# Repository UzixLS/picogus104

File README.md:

## PicoGUS/104
Gravis Ultrasound compatible sound card for IBM PC.

This is variant of [PicoGUS](https://picog.us/) v2.0 project by [Ian Scott](https://ianscott.org/) adapted for PC/104 bus. This variant also integrates SAM2695 MIDI synthesizer on board.

For details and firmware please follow this link: https://github.com/polpo/picogus

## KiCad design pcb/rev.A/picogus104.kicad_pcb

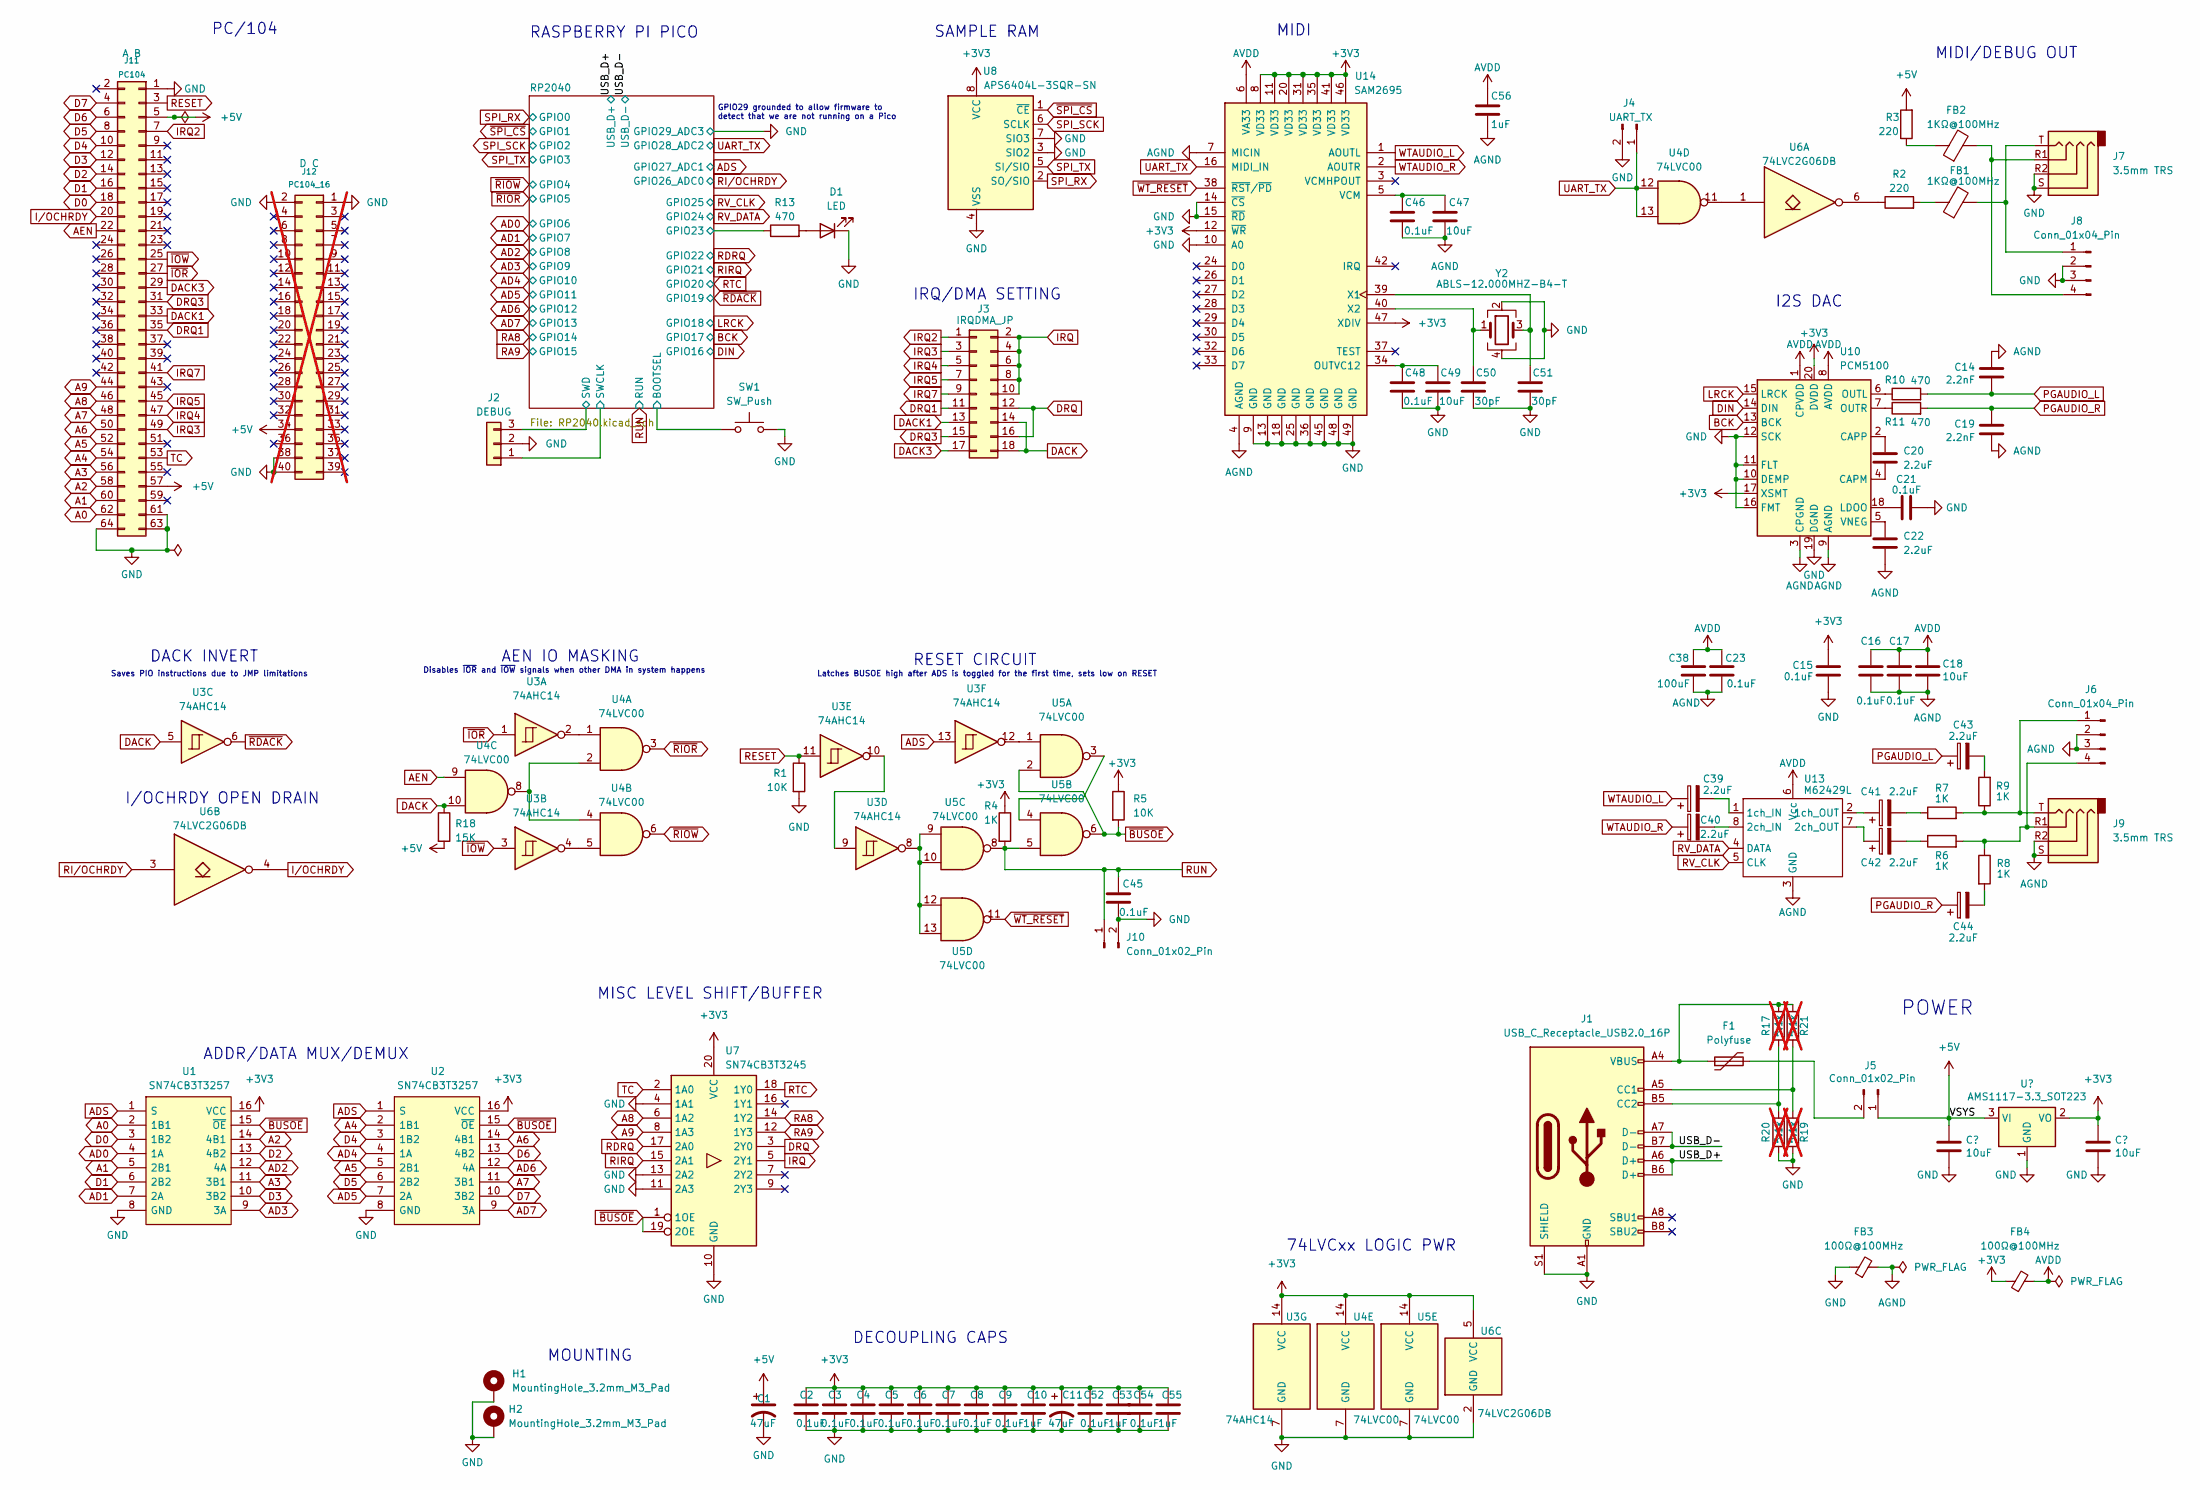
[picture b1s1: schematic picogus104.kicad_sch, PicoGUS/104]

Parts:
C1, C11: 47uF; C_1206_3216Metric
C2, C3, C4, C5, C6, C7, C8, C9, C15, C16, C17, C21, C23, C45, C46, C48, C52, C54: 0.1uF; C_0603_1608Metric_Pad1.08x0.95mm_HandSolder
C10, C53, C55, C56: 1uF; C_0603_1608Metric_Pad1.08x0.95mm_HandSolder
C12, C13, C18, C47, C49: 10uF; C_0805_2012Metric_Pad1.18x1.45mm_HandSolder
C14, C19: 2.2nF; C_0603_1608Metric_Pad1.08x0.95mm_HandSolder
C20, C22: 2.2uF; C_0603_1608Metric_Pad1.08x0.95mm_HandSolder
C38: 100uF; C_1206_3216Metric
C39, C40, C41, C42, C43, C44: 2.2uF; CP_Elec_4x5.4
C50, C51: 30pF; C_0603_1608Metric_Pad1.08x0.95mm_HandSolder
D1: LED; LED_0805_2012Metric_Pad1.15x1.40mm_HandSolder
F1: Polyfuse; Fuse_1812_4532Metric_Pad1.30x3.40mm_HandSolder
FB1, FB2: 1KΩ@100MHz; L_0805_2012Metric_Pad1.05x1.20mm_HandSolder
FB3, FB4: 100Ω@100MHz; L_0805_2012Metric_Pad1.05x1.20mm_HandSolder
H1, H2: MountingHole_3.2mm_M3_Pad
J1: USB_C_Receptacle_USB2.0_16P; USB_C_Receptacle_HRO_TYPE-C-31-M-12
J2: DEBUG; PinHeader_1x03_P2.54mm_Vertical
J3: IRQDMA_JP; PinHeader_2x09_P2.54mm_Vertical
J4: UART_TX; PinHeader_1x02_P2.54mm_Vertical
J5, J10: Conn_01x02_Pin; PinHeader_1x02_P2.54mm_Vertical
J6, J8: Conn_01x04_Pin; PinHeader_1x04_P2.54mm_Vertical
J7, J9: 3.5mm TRS; PJ-322
J11: PC104; PinHeader_2x32_P2.54mm_Vertical
J12: PC104_16; PinHeader_2x20_P2.54mm_Vertical; not fitted
R1, R5: 10K; R_0603_1608Metric_Pad0.98x0.95mm_HandSolder
R2, R3: 220; R_0603_1608Metric_Pad0.98x0.95mm_HandSolder
R4, R6, R7, R8, R9: 1K; R_0603_1608Metric_Pad0.98x0.95mm_HandSolder
R10, R11, R13: 470; R_0603_1608Metric_Pad0.98x0.95mm_HandSolder
R17, R19, R20, R21: 5.1k; R_0603_1608Metric_Pad0.98x0.95mm_HandSolder; not fitted
R18: 15K; R_0603_1608Metric_Pad0.98x0.95mm_HandSolder
SW1: SW_Push; SW_PUSH_6mm
U1, U2: SN74CB3T3257; TSSOP-16_4.4x5mm_P0.65mm; Manufacturer_Part_Number 74FST3257DR2G; Mouser Part Number 863-74FST3257DR2G
U3: 74AHC14; TSSOP-14_4.4x5mm_P0.65mm
U4, U5: 74LVC00; TSSOP-14_4.4x5mm_P0.65mm
U6: 74LVC2G06DB; SOT-23-6_Handsoldering
U7: SN74CB3T3245; TSSOP-20_4.4x6.5mm_P0.65mm
U8: APS6404L-3SQR-SN; SOIC-8_3.9x4.9mm_P1.27mm
U9: AMS1117-3.3_SOT223; SOT-223-3_TabPin2
U10: PCM5100; TSSOP-20_4.4x6.5mm_P0.65mm
U13: M62429L; SOIC-8_3.9x4.9mm_P1.27mm
U14: SAM2695; QFN-48-1EP_6x6mm_P0.4mm_EP4.2x4.2mm
Y2: ABLS-12.000MHZ-B4-T; Crystal_SMD_3225-4Pin_3.2x2.5mm_HandSoldering

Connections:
+3V3: C2.1, C3.1, C4.1, C5.1, C6.1, C7.1, C8.1, C9.1, C10.1, C11.1, C13.1, C15.2, C52.1, C53.1, C54.1, C55.1, FB4.1, R4.1, R5.1, U1.16 (VCC), U2.16 (VCC), U3.14 (VCC), U4.14 (VCC), U5.14 (VCC), U6.5 (VCC), U7.20 (VCC), U8.8 (VCC), U9.2 (VO), U10.17 (XSMT), U10.20 (DVDD), U14.8 (VD33), U14.11 (VD33), U14.12 (~WR), U14.20 (VD33), U14.31 (VD33), U14.35 (VD33), U14.41 (VD33), U14.46 (VD33), U14.47 (XDIV); also elsewhere on the board
+5V: C1.1, C12.1, J5.1, J11.5, J11.57, J12.34, R3.2, R18.2, U9.3 (VI)
/RP2040/GPIO23: R13.1; also elsewhere on the board
/RP2040/SWCLK: J2.1; also elsewhere on the board
/RP2040/SWD: J2.3; also elsewhere on the board
/RP2040/~USB_BOOT: SW1.2; also elsewhere on the board
/USB_D+: J1.A6 (D+), J1.B6 (D+); also elsewhere on the board
/USB_D-: J1.A7 (D-), J1.B7 (D-); also elsewhere on the board
A0: J11.62, U1.2 (1B1)
A1: J11.60, U1.5 (2B1)
A2: J11.58, U1.14 (4B1)
A3: J11.56, U1.11 (3B1)
A4: J11.54, U2.2 (1B1)
A5: J11.52, U2.5 (2B1)
A6: J11.50, U2.14 (4B1)
A7: J11.48, U2.11 (3B1)
A8: J11.46, U7.6 (1A2)
A9: J11.44, U7.8 (1A3)
AD0: U1.4 (1A); also elsewhere on the board
AD1: U1.7 (2A); also elsewhere on the board
AD2: U1.12 (4A); also elsewhere on the board
AD3: U1.9 (3A); also elsewhere on the board
AD4: U2.4 (1A); also elsewhere on the board
AD5: U2.7 (2A); also elsewhere on the board
AD6: U2.12 (4A); also elsewhere on the board
AD7: U2.9 (3A); also elsewhere on the board
ADS: U1.1 (S), U2.1 (S), U3.13; also elsewhere on the board
AEN: J11.22, U4.9
AGND: C14.1, C16.1, C17.1, C18.2, C19.1, C22.2, C23.2, C38.2, C46.1, C47.1, C56.2, FB3.2, J6.2, J6.3, J9.R2, J9.S, U10.3 (CPGND), U10.9 (AGND), U13.3 (GND), U14.4 (AGND), U14.7 (MICIN)
AVDD: C16.2, C17.2, C18.1, C23.1, C38.1, C56.1, FB4.2, U10.1 (CPVDD), U10.8 (AVDD), U13.6 (Vcc), U14.6 (VA33)
BCK: U10.13 (BCK); also elsewhere on the board
D0: J11.18, U1.3 (1B2)
D1: J11.16, U1.6 (2B2)
D2: J11.14, U1.13 (4B2)
D3: J11.12, U1.10 (3B2)
D4: J11.10, U2.3 (1B2)
D5: J11.8, U2.6 (2B2)
D6: J11.6, U2.13 (4B2)
D7: J11.4, U2.10 (3B2)
DACK: J3.14, J3.18, R18.1, U3.5, U4.10
DACK1: J3.13, J11.33
DACK3: J3.17, J11.29
DIN: U10.14 (DIN); also elsewhere on the board
DRQ: J3.12, J3.16, U7.3 (2Y0)
DRQ1: J3.11, J11.35
DRQ3: J3.15, J11.31
GND: C1.2, C2.2, C3.2, C4.2, C5.2, C6.2, C7.2, C8.2, C9.2, C10.2, C11.2, C12.2, C13.2, C15.1, C21.2, C45.2, C48.1, C49.1, C50.1, C51.1, C52.2, C53.2, C54.2, C55.2, D1.1 (K), FB3.1, H1.1, H2.1, J1.A1 (GND), J1.A12 (GND), J1.B1 (GND), J1.B12 (GND), J1.S1 (SHIELD), J2.2, J4.2, J7.R2, J7.S, J8.2, J8.3, J10.2, J11.1, J11.61, J11.63, J11.64, J12.1, J12.2, J12.38, J12.40, R1.2, R19.1, R20.1, SW1.1, U1.8 (GND), U2.8 (GND), U3.7 (GND), U4.7 (GND), U5.7 (GND), U6.2 (GND), U7.4 (1A1), U7.10 (GND), U7.11 (2A3), U7.13 (2A2), U8.3 (SIO2), U8.4 (VSS), U8.7 (SIO3), U9.1 (GND), U10.10 (DEMP), U10.11 (FLT), U10.12 (SCK), U10.16 (FMT), U10.19 (DGND), U14.9 (GND), U14.10 (A0), U14.13 (GND), U14.14 (~CS), U14.15 (~RD), U14.18 (GND), U14.25 (GND), U14.36 (GND), U14.45 (GND), U14.48 (GND), U14.49 (GND), Y2.2, Y2.4; also elsewhere on the board
IRQ: J3.2, J3.4, J3.6, J3.8, J3.10, U7.5 (2Y1)
IRQ2: J3.1, J11.7
IRQ3: J3.3, J11.49
IRQ4: J3.5, J11.47
IRQ5: J3.7, J11.45
IRQ7: J3.9, J11.41
I/OCHRDY: J11.20, U6.4
LRCK: U10.15 (LRCK); also elsewhere on the board
unnamed: C41.2, R7.1
unnamed: C42.2, R6.1
unnamed: C43.2, R9.2
unnamed: C44.2, R8.2
unnamed: D1.2 (A), R13.2
unnamed: F1.1, J1.A4 (VBUS), J1.A9 (VBUS), J1.B4 (VBUS), J1.B9 (VBUS), R17.2, R21.2
unnamed: FB1.1, R2.2
unnamed: FB2.1, R3.1
unnamed: J1.A5 (CC1), R19.2, R21.1
unnamed: J1.B5 (CC2), R17.1, R20.2
unnamed: F1.2, J5.2
unnamed: J6.1, J9.T, R7.2, R9.1
unnamed: J6.4, J9.R1, R6.2, R8.1
unnamed: FB1.2, J7.T, J8.1
unnamed: FB2.2, J7.R1, J8.4
unnamed: R2.1, U6.6
unnamed: U3.2, U4.1
unnamed: U3.4, U4.5
unnamed: U3.8, U5.9, U5.10, U5.12, U5.13
unnamed: U3.9, U3.10
unnamed: U3.12, U5.1
unnamed: U4.2, U4.4, U4.8
unnamed: U4.11, U6.1
unnamed: U5.3, U5.4
unnamed: C20.2, U10.4 (CAPM)
unnamed: C20.1, U10.2 (CAPP)
unnamed: C21.1, U10.18 (LDOO)
unnamed: R10.1, U10.6 (OUTL)
unnamed: R11.1, U10.7 (OUTR)
unnamed: C22.1, U10.5 (VNEG)
unnamed: C39.2, U13.1 (1ch_IN)
unnamed: C41.1, U13.2 (1ch_OUT)
unnamed: C40.2, U13.8 (2ch_IN)
unnamed: C42.1, U13.7 (2ch_OUT)
unnamed: C48.2, C49.2, U14.34 (OUTVC12)
unnamed: C46.2, C47.2, U14.5 (VCM)
unnamed: C51.2, U14.39 (X1), Y2.3
unnamed: C50.2, U14.40 (X2), Y2.1
PGAUDIO_L: C14.2, C43.1, R10.2
PGAUDIO_R: C19.2, C44.1, R11.2
RA8: U7.14 (1Y2); also elsewhere on the board
RA9: U7.12 (1Y3); also elsewhere on the board
RDRQ: U7.17 (2A0); also elsewhere on the board
RESET: J11.3, R1.1, U3.11
RIRQ: U7.15 (2A1); also elsewhere on the board
RI/OCHRDY: U6.3; also elsewhere on the board
RTC: U7.18 (1Y0); also elsewhere on the board
RUN: C45.1, J10.1, R4.2, U5.5, U5.8; also elsewhere on the board
RV_CLK: U13.5 (CLK); also elsewhere on the board
RV_DATA: U13.4 (DATA); also elsewhere on the board
SPI_RX: U8.2 (SO/SIO); also elsewhere on the board
SPI_SCK: U8.6 (SCLK); also elsewhere on the board
SPI_TX: U8.5 (SI/SIO); also elsewhere on the board
TC: J11.53, U7.2 (1A0)
UART_TX: J4.1, U4.12, U4.13, U14.16 (MIDI_IN); also elsewhere on the board
WTAUDIO_L: C39.1, U14.1 (AOUTL)
WTAUDIO_R: C40.1, U14.2 (AOUTR)
~BUSOE: R5.2, U1.15 (~OE), U2.15 (~OE), U5.2, U5.6, U7.1 (1OE), U7.19 (2OE)
~IOR: J11.27, U3.1
~IOW: J11.25, U3.3
~RDACK: U3.6; also elsewhere on the board
~RIOR: U4.3; also elsewhere on the board
~RIOW: U4.6; also elsewhere on the board
~SPI_CS: U8.1 (~CE); also elsewhere on the board
~WT_RESET: U5.11, U14.38 (~RST/~PD)

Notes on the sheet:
Saves PIO instructions due to JMP limitations
DECOUPLING CAPS
GPIO29 grounded to allow firmware to detect that we are not running on a Pico
I2S DAC
Disables ~{IOR} and ~{IOW} signals when other DMA in system happens
Latches BUSOE high after ADS is toggled for the first time, sets low on RESET
MIDI/DEBUG OUT
MOUNTING
MISC LEVEL SHIFT/BUFFER
IRQ/DMA SETTING
POWER
DACK INVERT
ADDR/DATA MUX/DEMUX
SAMPLE RAM
PC/104
AEN IO MASKING
RASPBERRY PI PICO
MIDI
RESET CIRCUIT
I/OCHRDY OPEN DRAIN
74LVCxx LOGIC PWR

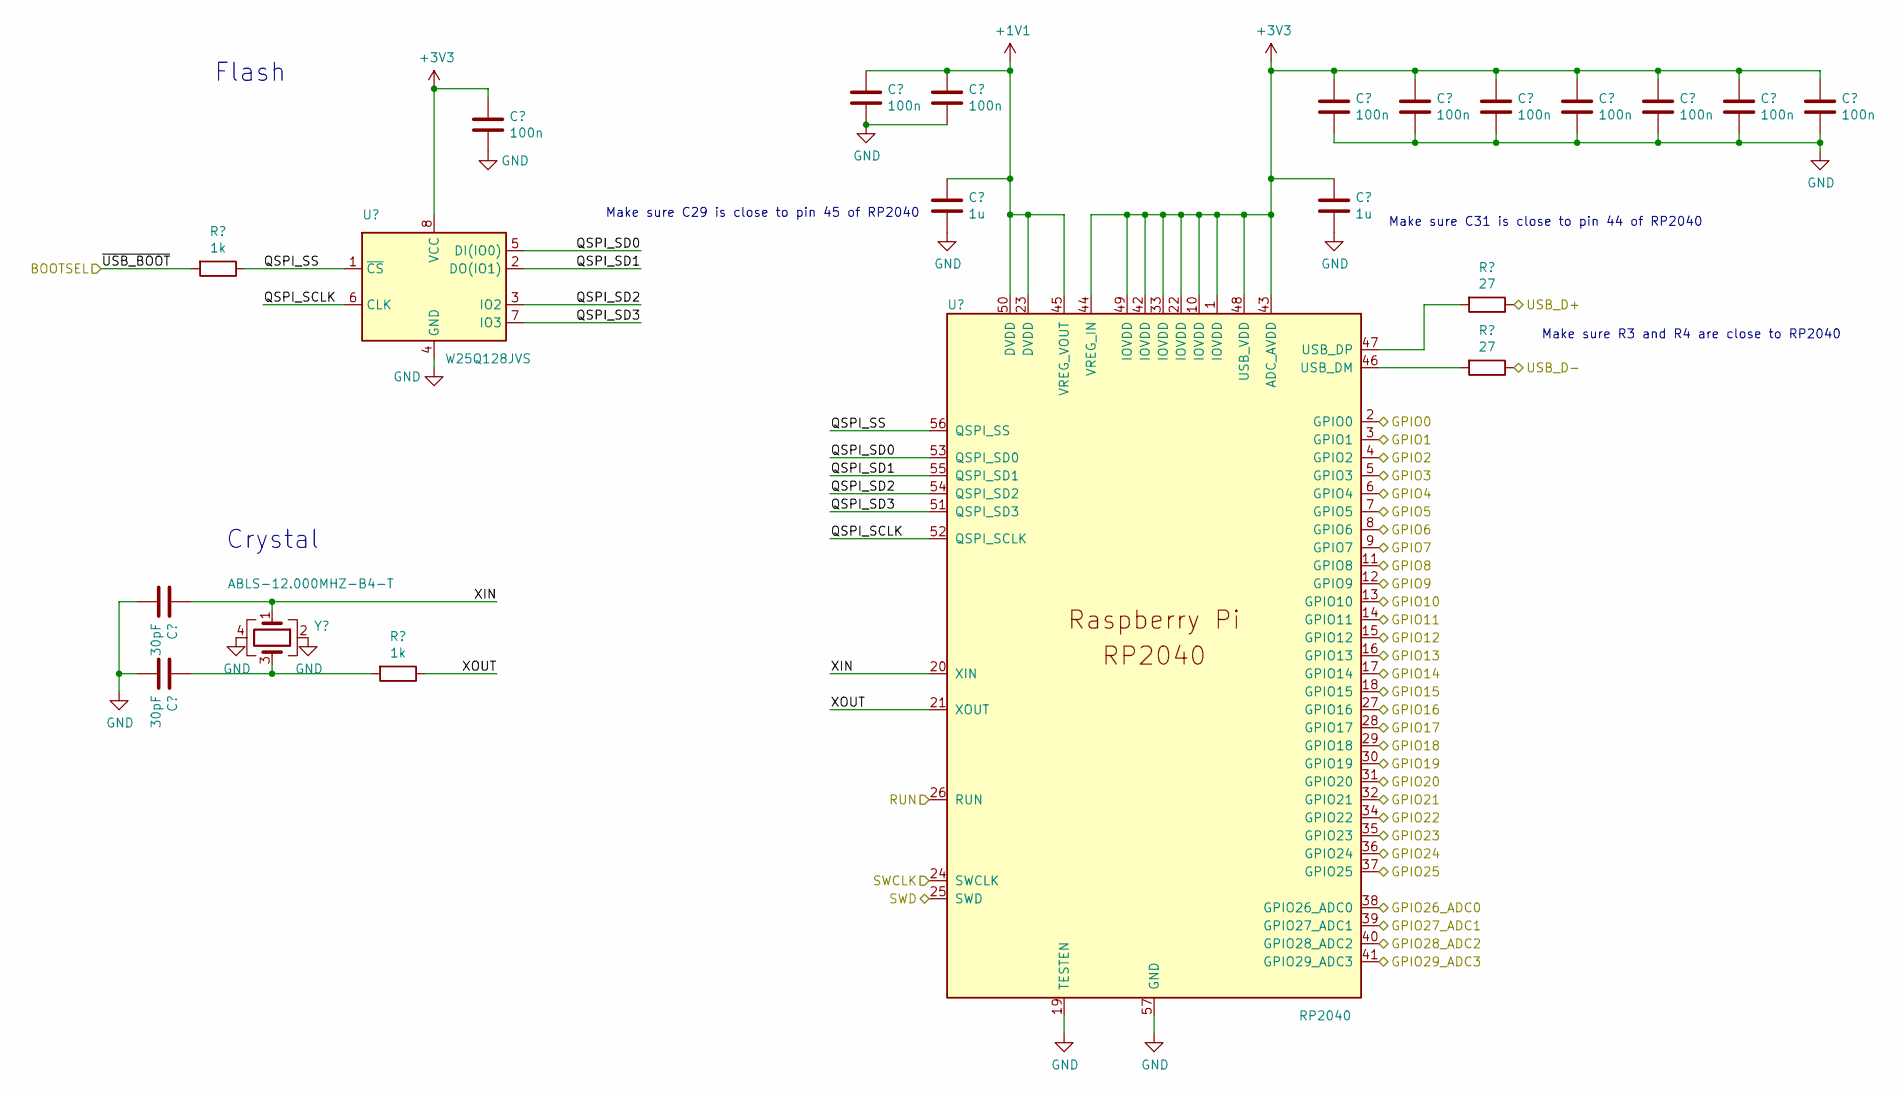
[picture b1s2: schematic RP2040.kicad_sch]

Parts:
C24, C25: 30pF; C_0603_1608Metric_Pad1.08x0.95mm_HandSolder
C26, C27, C28, C30, C32, C33, C34, C35, C36, C37: 100n; C_0603_1608Metric_Pad1.08x0.95mm_HandSolder
C29, C31: 1u; C_0603_1608Metric_Pad1.08x0.95mm_HandSolder
R12, R14: 1k; R_0603_1608Metric_Pad0.98x0.95mm_HandSolder
R15, R16: 27; R_0603_1608Metric_Pad0.98x0.95mm_HandSolder
U11: W25Q128JVS; SOIC-8_5.23x5.23mm_P1.27mm-LONG
U12: RP2040; QFN-56-1EP_7x7mm_P0.4mm_EP3.2x3.2mm
Y1: ABLS-12.000MHZ-B4-T; Crystal_SMD_3225-4Pin_3.2x2.5mm_HandSoldering

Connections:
+1V1: C27.1, C28.1, C29.1, U12.23 (DVDD), U12.45 (VREG_VOUT), U12.50 (DVDD)
+3V3: C26.1, C30.1, C31.1, C32.1, C33.1, C34.1, C35.1, C36.1, C37.1, U11.8 (VCC), U12.1 (IOVDD), U12.10 (IOVDD), U12.22 (IOVDD), U12.33 (IOVDD), U12.42 (IOVDD), U12.43 (ADC_AVDD), U12.44 (VREG_IN), U12.48 (USB_VDD), U12.49 (IOVDD); also elsewhere on the board
/RP2040/GPIO23: U12.35 (GPIO23); also elsewhere on the board
/RP2040/QSPI_SCLK: U11.6 (CLK), U12.52 (QSPI_SCLK)
/RP2040/QSPI_SD0: U11.5 (DI(IO0)), U12.53 (QSPI_SD0)
/RP2040/QSPI_SD1: U11.2 (DO(IO1)), U12.55 (QSPI_SD1)
/RP2040/QSPI_SD2: U11.3 (IO2), U12.54 (QSPI_SD2)
/RP2040/QSPI_SD3: U11.7 (IO3), U12.51 (QSPI_SD3)
/RP2040/QSPI_SS: R12.1, U11.1 (~CS), U12.56 (QSPI_SS)
/RP2040/SWCLK: U12.24 (SWCLK); also elsewhere on the board
/RP2040/SWD: U12.25 (SWD); also elsewhere on the board
/RP2040/XIN: C24.1, U12.20 (XIN), Y1.1
/RP2040/XOUT: R14.1, U12.21 (XOUT)
/RP2040/~USB_BOOT: R12.2; also elsewhere on the board
/USB_D+: R15.1; also elsewhere on the board
/USB_D-: R16.1; also elsewhere on the board
AD0: U12.8 (GPIO6); also elsewhere on the board
AD1: U12.9 (GPIO7); also elsewhere on the board
AD2: U12.11 (GPIO8); also elsewhere on the board
AD3: U12.12 (GPIO9); also elsewhere on the board
AD4: U12.13 (GPIO10); also elsewhere on the board
AD5: U12.14 (GPIO11); also elsewhere on the board
AD6: U12.15 (GPIO12); also elsewhere on the board
AD7: U12.16 (GPIO13); also elsewhere on the board
ADS: U12.39 (GPIO27_ADC1); also elsewhere on the board
BCK: U12.28 (GPIO17); also elsewhere on the board
DIN: U12.27 (GPIO16); also elsewhere on the board
GND: C24.2, C25.2, C26.2, C27.2, C28.2, C29.2, C30.2, C31.2, C32.2, C33.2, C34.2, C35.2, C36.2, C37.2, U11.4 (GND), U12.19 (TESTEN), U12.41 (GPIO29_ADC3), U12.57 (GND), Y1.2, Y1.4; also elsewhere on the board
LRCK: U12.29 (GPIO18); also elsewhere on the board
unnamed: C25.1, R14.2, Y1.3
unnamed: R16.2, U12.46 (USB_DM)
unnamed: R15.2, U12.47 (USB_DP)
RA8: U12.17 (GPIO14); also elsewhere on the board
RA9: U12.18 (GPIO15); also elsewhere on the board
RDRQ: U12.34 (GPIO22); also elsewhere on the board
RIRQ: U12.32 (GPIO21); also elsewhere on the board
RI/OCHRDY: U12.38 (GPIO26_ADC0); also elsewhere on the board
RTC: U12.31 (GPIO20); also elsewhere on the board
RUN: U12.26 (RUN); also elsewhere on the board
RV_CLK: U12.37 (GPIO25); also elsewhere on the board
RV_DATA: U12.36 (GPIO24); also elsewhere on the board
SPI_RX: U12.2 (GPIO0); also elsewhere on the board
SPI_SCK: U12.4 (GPIO2); also elsewhere on the board
SPI_TX: U12.5 (GPIO3); also elsewhere on the board
UART_TX: U12.40 (GPIO28_ADC2); also elsewhere on the board
~RDACK: U12.30 (GPIO19); also elsewhere on the board
~RIOR: U12.7 (GPIO5); also elsewhere on the board
~RIOW: U12.6 (GPIO4); also elsewhere on the board
~SPI_CS: U12.3 (GPIO1); also elsewhere on the board

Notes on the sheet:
Make sure R3 and R4 are close to RP2040
Make sure C29 is close to pin 45 of RP2040
Make sure C31 is close to pin 44 of RP2040
Flash
Crystal

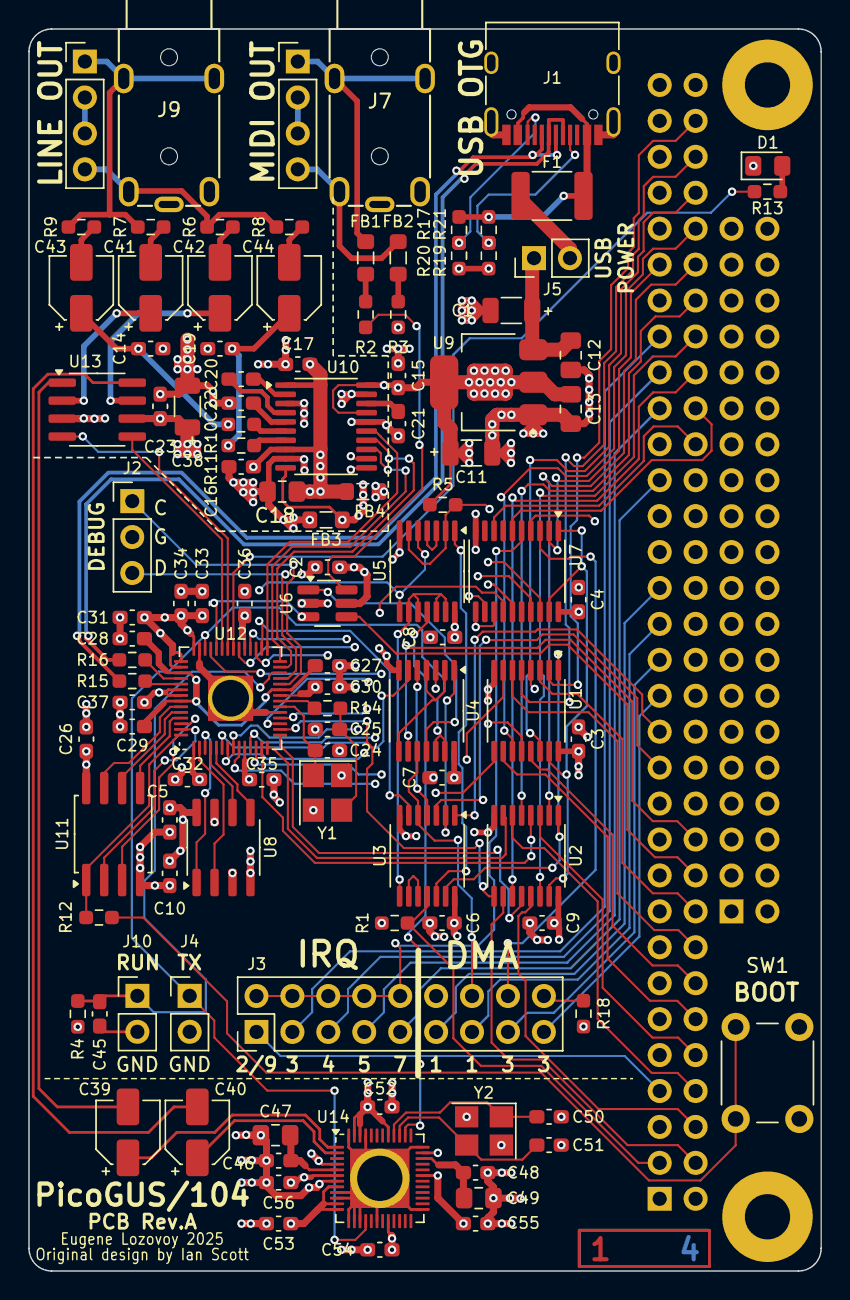
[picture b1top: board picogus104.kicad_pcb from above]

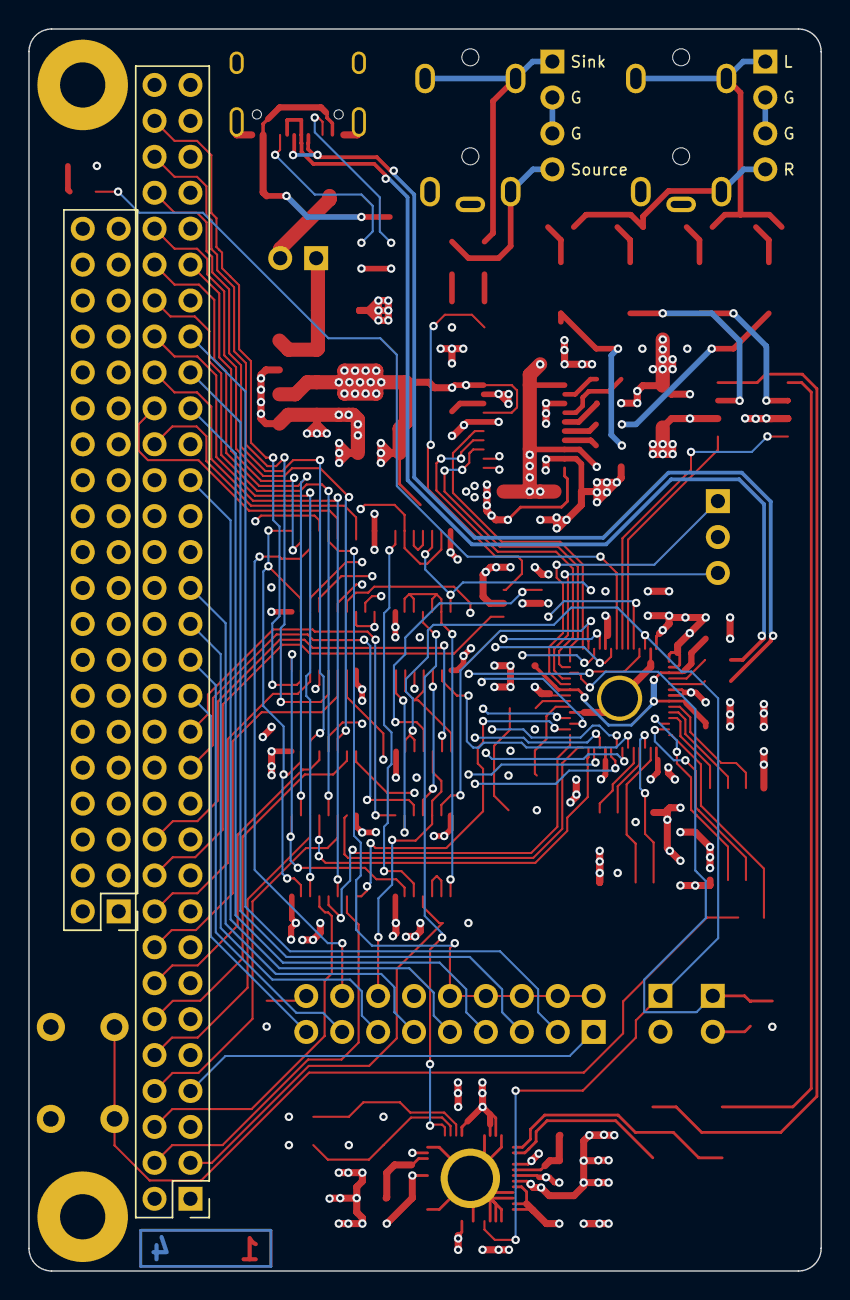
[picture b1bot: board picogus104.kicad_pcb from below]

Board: 4 copper layers, 56.0 x 87.8 mm, 114 parts (2 on the bottom side), 132 nets.

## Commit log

2024-12-24 init
2024-12-24 wip pcb rev.A
2025-01-01 wip pcb reb.A - almost done
2025-03-19 pcb rev.A - final version
2025-03-19 add readme
2025-03-21 bom fixes
2025-03-29 release pcb rev.A
2026-06-17 remove raw=true from README links
